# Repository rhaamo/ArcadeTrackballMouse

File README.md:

# Mouse-Trak drop-in PCB v2

Got an old 1998 MOUSE-TRAK but the Z86 MCU seems fried.

This project is based on the trackball PCBs and Firmware of the 
https://source.mntmn.com/MNT/reform Open Source Portable Computer.

See LICENSES for informations.

## CHANGES

- imported the trackball two PCBs and firmware

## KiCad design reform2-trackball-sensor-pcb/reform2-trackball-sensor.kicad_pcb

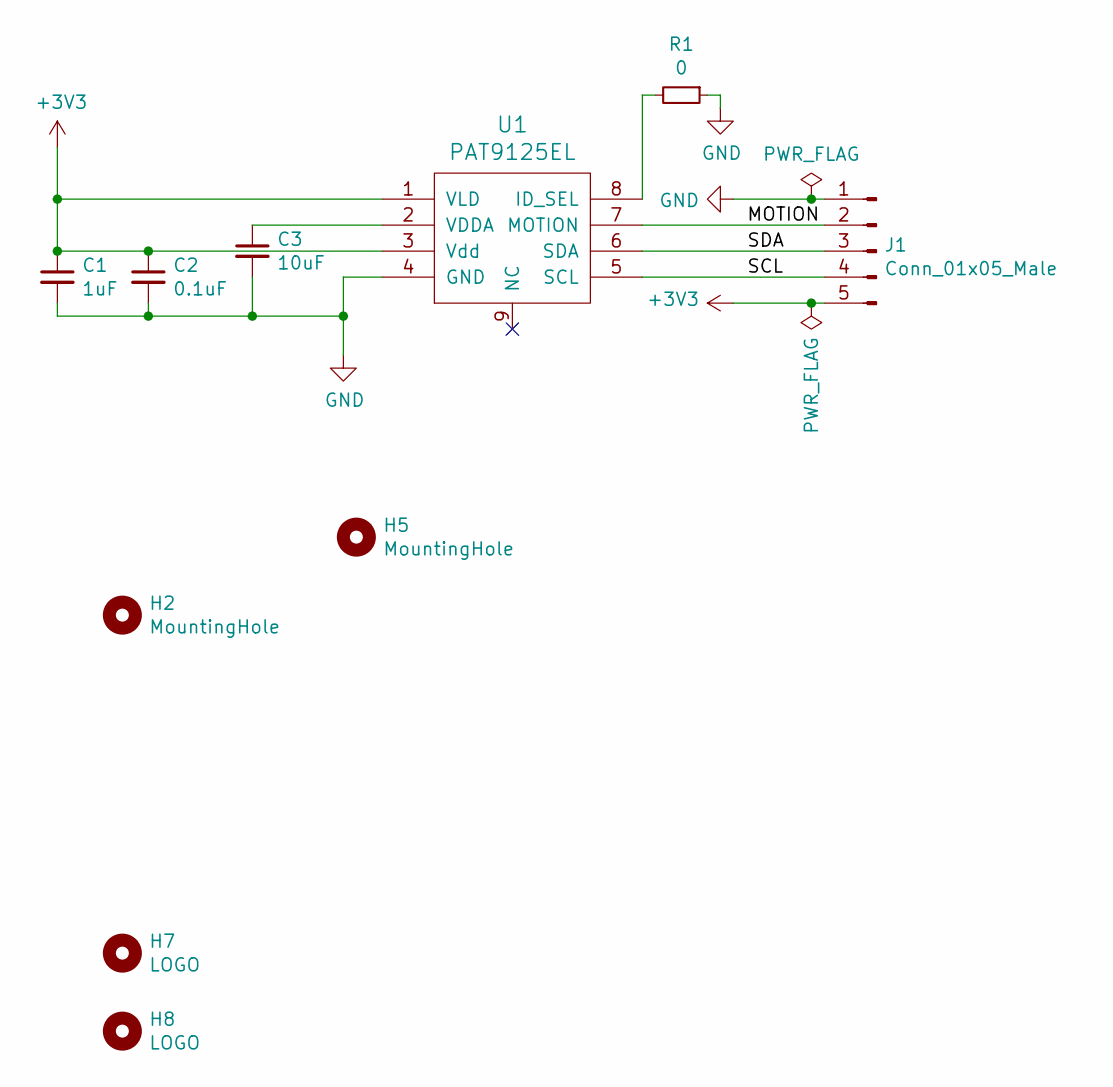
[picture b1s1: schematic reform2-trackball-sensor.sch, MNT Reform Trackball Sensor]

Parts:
C1: 1uF; C_0603_1608Metric
C2: 0.1uF; C_0603_1608Metric
C3: 10uF; C_0603_1608Metric
H2, H5: MountingHole; MountingHole_2.2mm_M2
H7, H8: LOGO; mnt-minilogo
J1: Conn_01x05_Male; PinHeader_1x05_P2.54mm_Horizontal
R1: 0; R_0603_1608Metric
U1: PAT9125EL

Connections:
+3V3: C1.1, C2.1, J1.5, U1.1 (VLD), U1.3 (Vdd)
/MOTION: J1.2, U1.7 (MOTION)
/SCL: J1.4, U1.5 (SCL)
/SDA: J1.3, U1.6 (SDA)
GND: C1.2, C2.2, C3.2, J1.1, R1.1, U1.4 (GND)
unnamed: C3.1, U1.2 (VDDA)
unnamed: R1.2, U1.8 (ID_SEL)

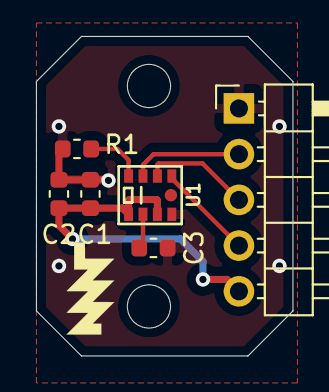
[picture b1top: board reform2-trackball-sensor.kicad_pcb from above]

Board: 2 copper layers, 14.2 x 17.8 mm, 10 parts (1 on the bottom side), 7 nets.

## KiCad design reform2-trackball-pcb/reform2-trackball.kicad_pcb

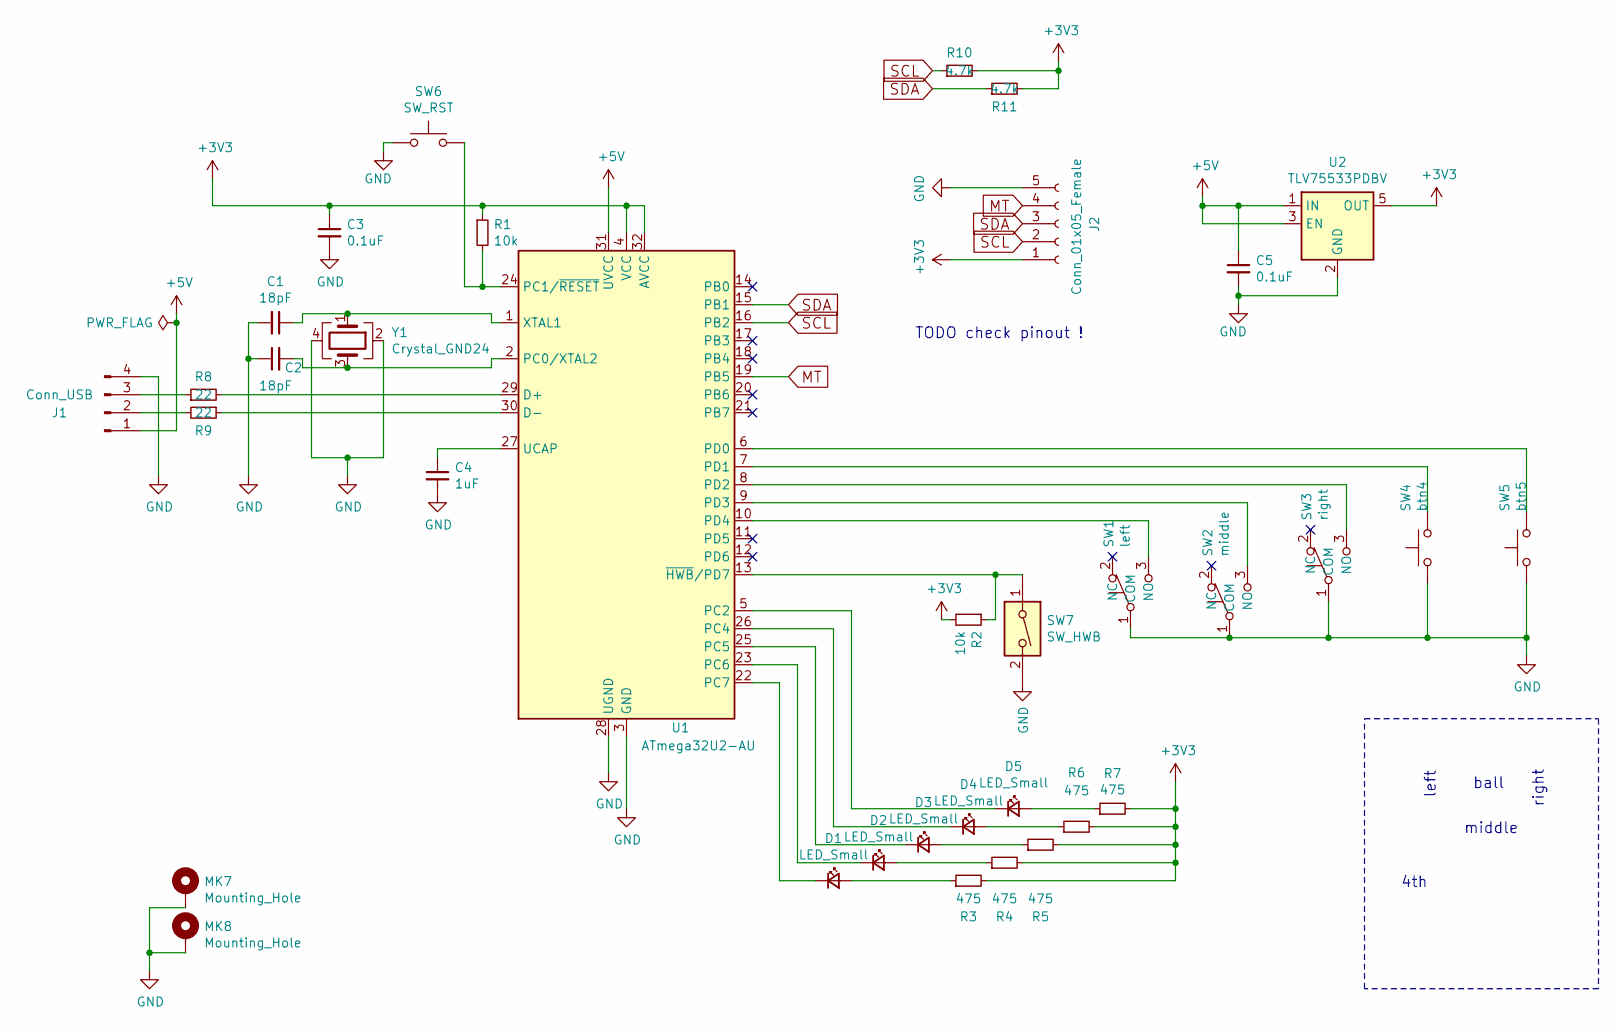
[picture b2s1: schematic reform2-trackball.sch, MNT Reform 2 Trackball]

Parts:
C1, C2: 18pF; C_0603_1608Metric
C3, C5: 0.1uF; C_0603_1608Metric
C4: 1uF; C_0603_1608Metric
D1, D2, D3, D4, D5: LED_Small; LED_0603_1608Metric
J1: Conn_USB; JST_PH_B4B-PH-K_1x04_P2.00mm_Vertical
J2: Conn_01x05_Female; PinSocket_1x05_P2.54mm_Vertical
MK7, MK8: Mounting_Hole; MountingHole_2.2mm_M2_Pad
R1, R2: 10k; R_0603_1608Metric
R3, R4, R5, R6, R7: 475; R_0603_1608Metric
R8, R9: 22; R_0603_1608Metric
R10, R11: 4.7k; R_0603_1608Metric
SW1: left; SubminiatureSPDT
SW2: middle; SubminiatureSPDT
SW3: right; SubminiatureSPDT
SW4: btn4; Push_E-Switch_KS01Q01
SW5: btn5; PinHeader_1x02_P2.54mm_Vertical
SW6: SW_RST; SW_Push_1P1T_NO_CK_KMR2
SW7: SW_HWB; SW_DIP_SPSTx01_Slide_Omron_A6S-110x_W8.9mm_P2.54mm
U1: ATmega32U2-AU; TQFP-32_7x7mm_Pitch0.8mm
U2: TLV75533PDBV; SOT-23-5
Y1: Crystal_GND24; Crystal_SMD_3225-4pin_3.2x2.5mm_HandSoldering

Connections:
+3V3: C3.1, J2.1, R1.1, R2.2, R3.2, R4.2, R5.2, R6.2, R7.2, R10.2, R11.2, U1.4 (VCC), U1.32 (AVCC), U2.5 (OUT)
+5V: C5.1, J1.1, U1.31 (UVCC), U2.1 (IN), U2.3 (EN)
GND: C1.2, C2.1, C3.2, C4.2, C5.2, J1.4, J2.5, MK7.1, MK8.1, SW1.1 (COM), SW2.1 (COM), SW3.1 (COM), SW4.1, SW5.1, SW6.1, SW7.2, U1.3 (GND), U1.28 (UGND), U2.2 (GND), Y1.2, Y1.4
MT: J2.4, U1.19 (PB5)
unnamed: C1.1, U1.1 (XTAL1), Y1.1
unnamed: C2.2, U1.2 (PC0/XTAL2), Y1.3
unnamed: C4.1, U1.27 (UCAP)
unnamed: D1.1 (K), U1.22 (PC7)
unnamed: D1.2 (A), R3.1
unnamed: D2.1 (K), U1.23 (PC6)
unnamed: D2.2 (A), R4.1
unnamed: D3.1 (K), U1.25 (PC5)
unnamed: D3.2 (A), R5.1
unnamed: D4.1 (K), U1.26 (PC4)
unnamed: D4.2 (A), R6.1
unnamed: D5.1 (K), U1.5 (PC2)
unnamed: D5.2 (A), R7.1
unnamed: J1.2, R9.2
unnamed: J1.3, R8.1
unnamed: R1.2, SW6.2, U1.24 (PC1/~RESET)
unnamed: R2.1, SW7.1, U1.13 (~HWB~/PD7)
unnamed: R8.2, U1.29 (D+)
unnamed: R9.1, U1.30 (D-)
unnamed: SW1.3 (NO), U1.10 (PD4)
unnamed: SW2.3 (NO), U1.9 (PD3)
unnamed: SW3.3 (NO), U1.8 (PD2)
unnamed: SW4.2, U1.7 (PD1)
unnamed: SW5.2, U1.6 (PD0)
SCL: J2.2, R10.1, U1.16 (PB2)
SDA: J2.3, R11.1, U1.15 (PB1)

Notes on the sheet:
TODO check pinout !
ball
middle
right
left
4th

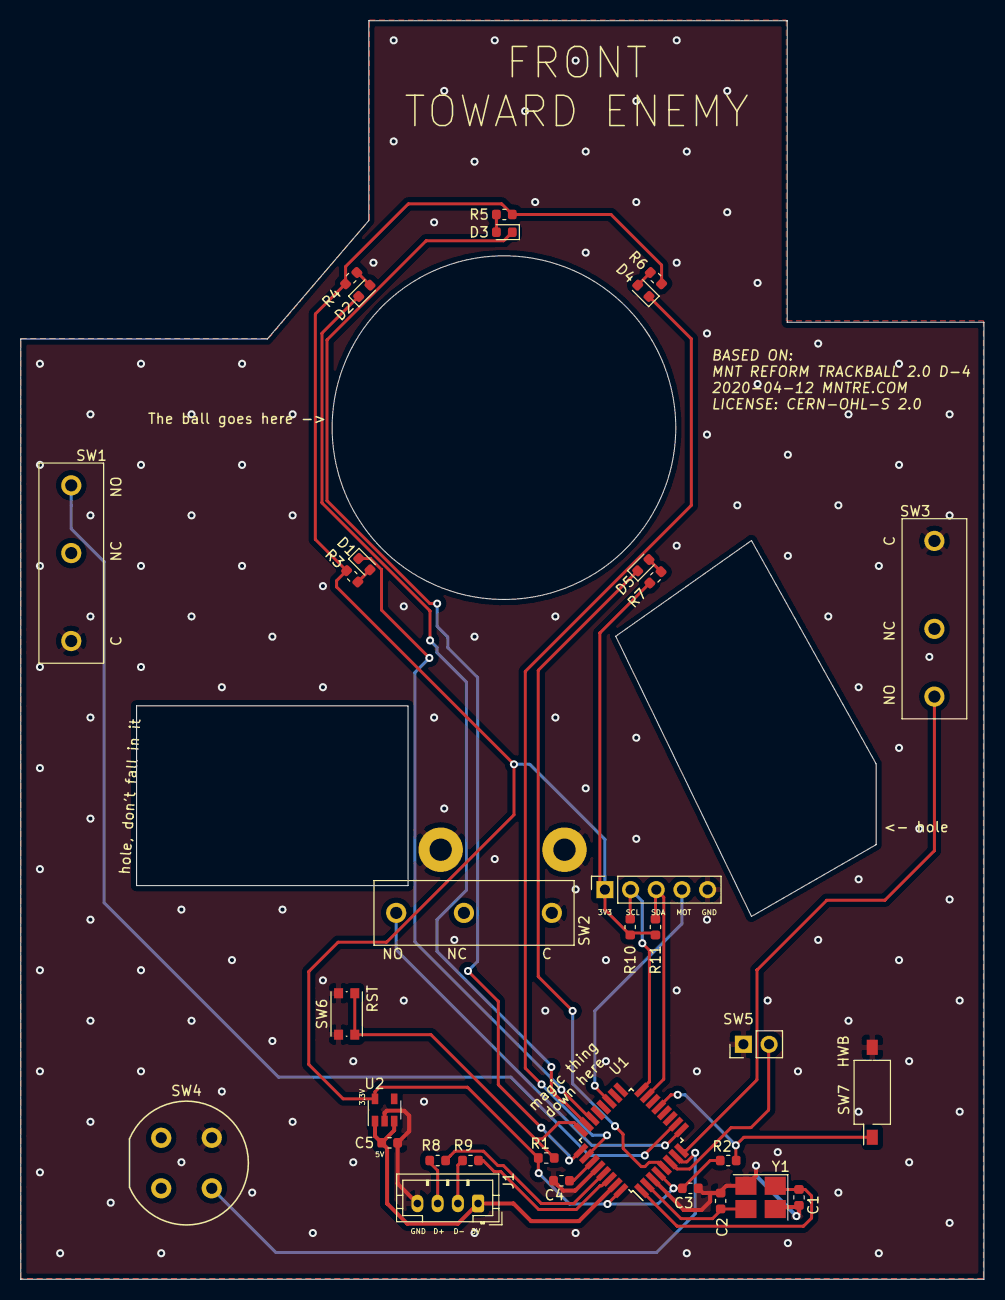
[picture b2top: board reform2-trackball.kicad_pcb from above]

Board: 2 copper layers, 95.3 x 124.5 mm, 35 parts (0 on the bottom side), 30 nets.

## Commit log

2019-08-07 We don't use that
2019-08-07 We don't have led, change pins for teensy 2.0
2019-08-09 Move firmware to use platformio
2020-09-30 Import PCBs
2020-09-30 Hardware changes for the mouse-trak
2020-10-04 new pcb
2020-10-17 squeak
2020-10-17 ibom

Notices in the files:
reform2-trackball-pcb/reform2-trackball.kicad_pcb:
LICENSE: CERN-OHL-S 2.0
reform2-trackball-pcb/reform2-trackball.sch:
Copyright 2017-2020 MNT Research GmbH
